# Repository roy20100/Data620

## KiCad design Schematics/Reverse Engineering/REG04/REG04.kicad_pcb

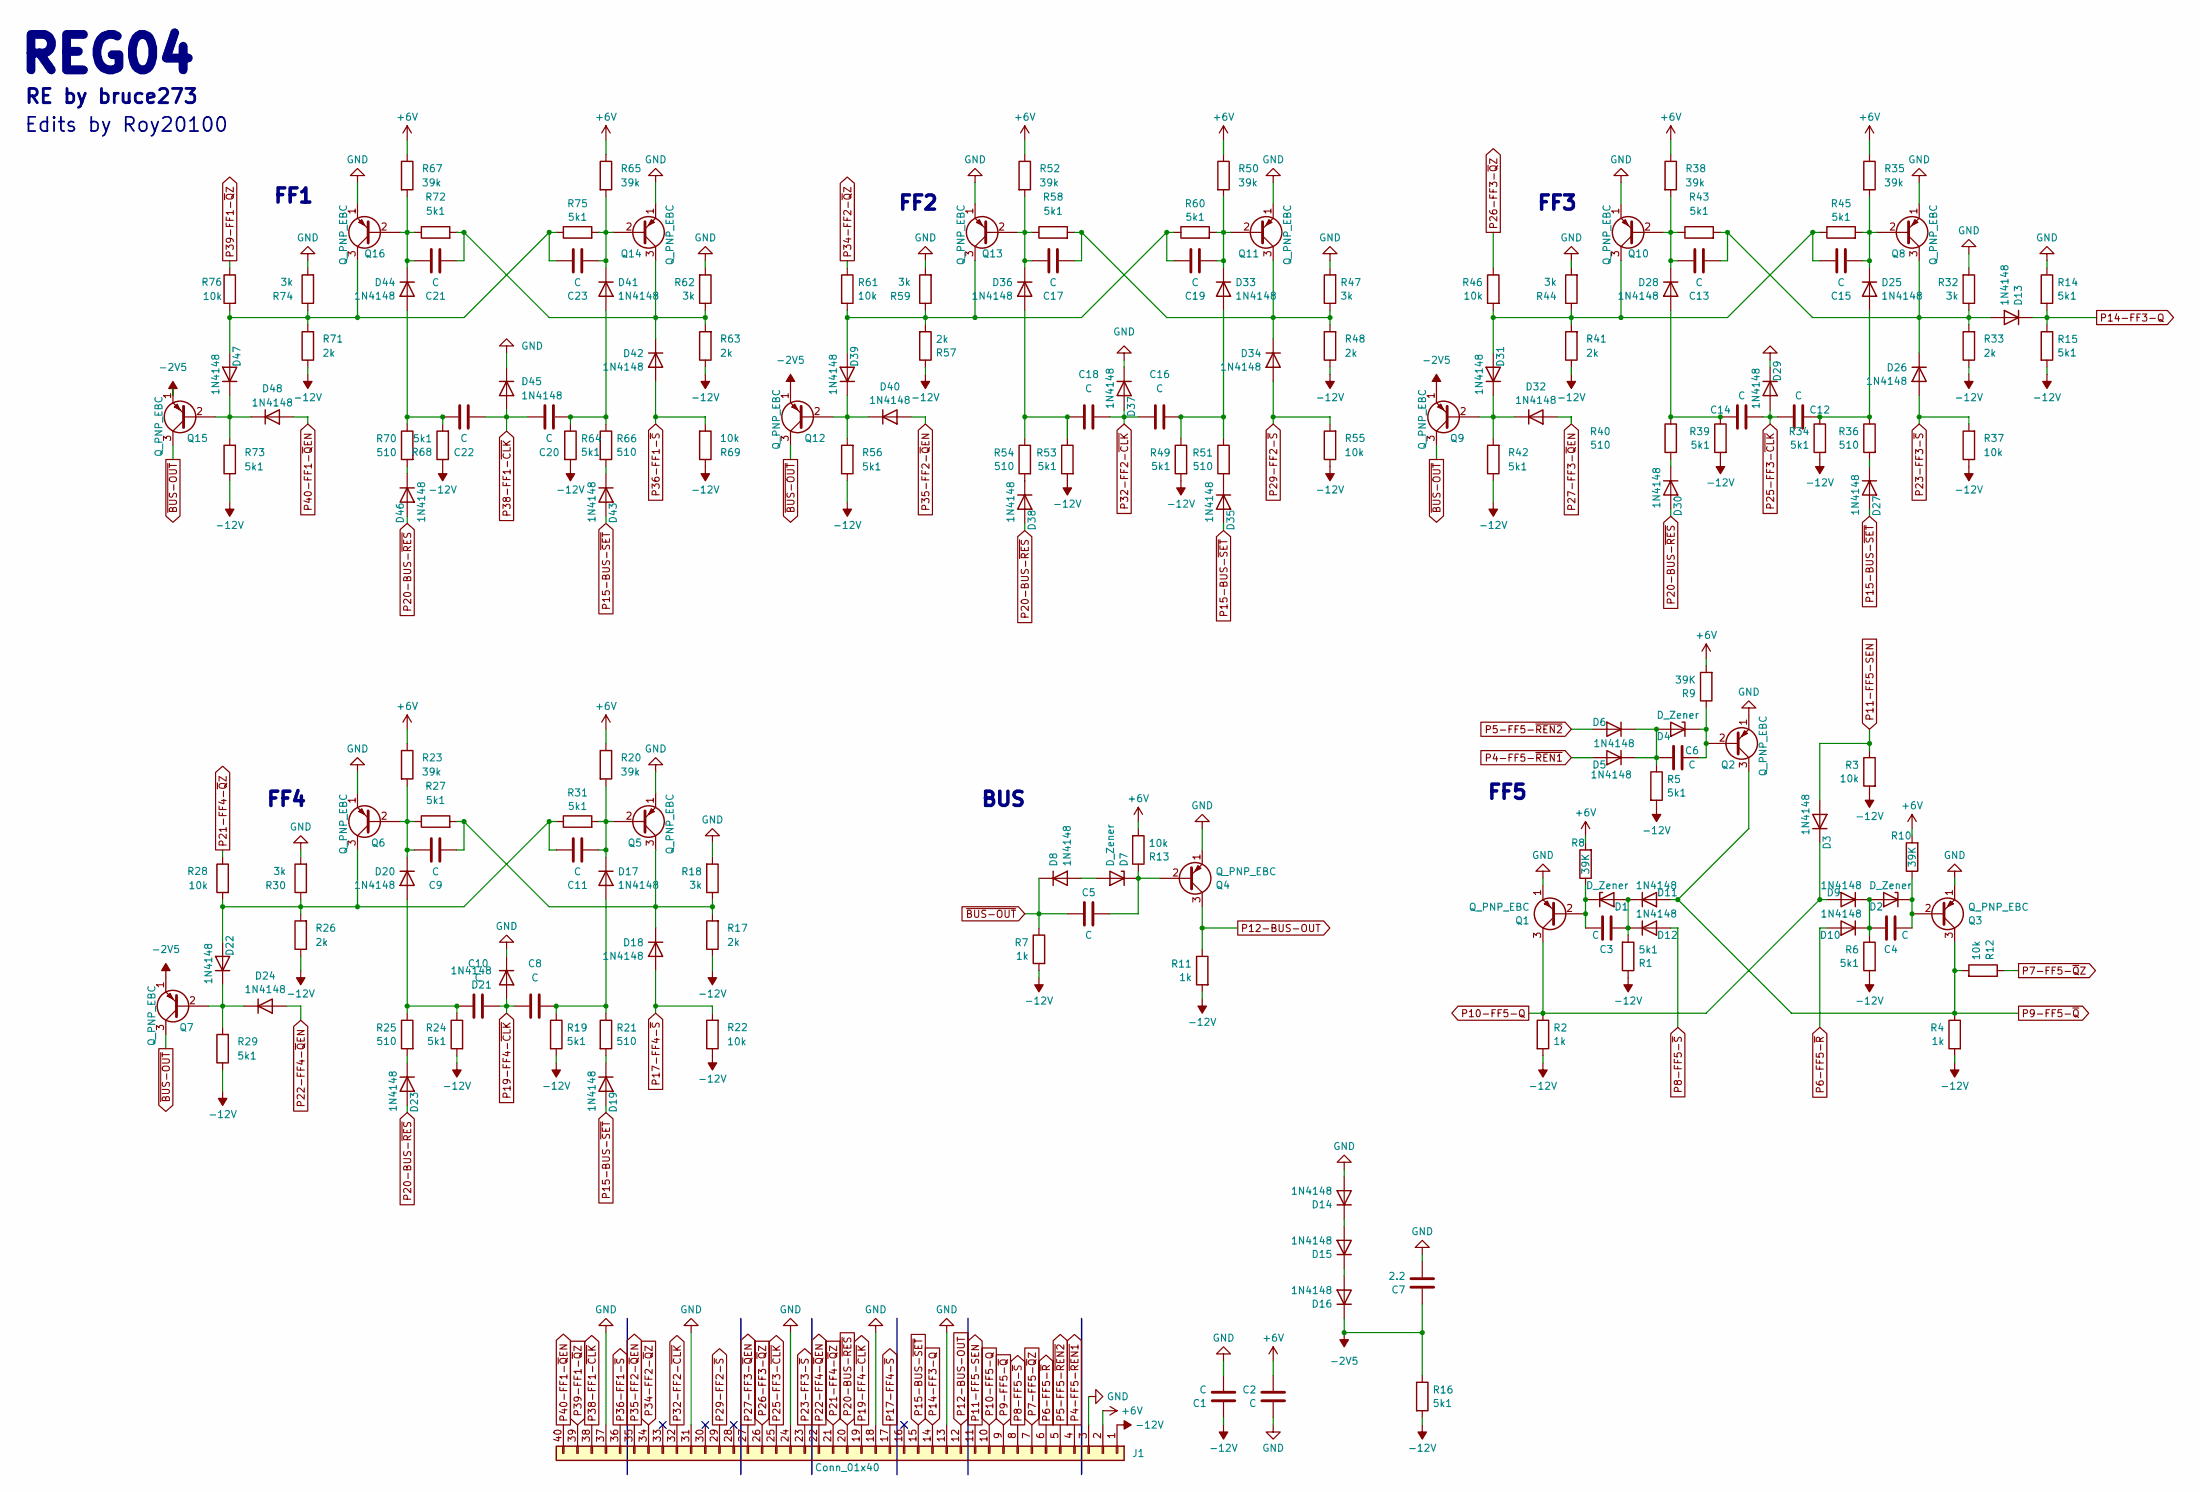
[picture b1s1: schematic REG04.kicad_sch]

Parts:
C1: C; C_Axial_L5.1mm_D3.1mm_P12.50mm_Horizontal
C2: C; C_Axial_L12.0mm_D6.5mm_P15.00mm_Horizontal
C3, C4, C5, C6, C8, C9, C10, C11, C12, C13, C14, C15, C16, C17, C18, C19, C20, C21, C22, C23: C; C_Rect_L7.0mm_W2.0mm_P5.00mm
C7: 2.2; C_Axial_L5.1mm_D3.1mm_P12.50mm_Horizontal
D1, D2, D4, D7: D_Zener; D_A-405_P12.70mm_Horizontal
D3, D5, D6, D8, D9, D10, D11, D12, D13, D14, D15, D16, D17, D18, D19, D20, D21, D22, D23, D24, D25, D26, D27, D28, D29, D30, D31, D32, D33, D34, D35, D36, D37, D38, D39, D40, D41, D42, D43, D44, D45, D46, D47, D48: 1N4148; D_A-405_P12.70mm_Horizontal
J1: Conn_01x40; ELCO 40
Q1, Q2, Q3, Q4, Q5, Q6, Q7, Q8, Q9, Q10, Q11, Q12, Q13, Q14, Q15, Q16: Q_PNP_EBC; TO-5-3
R1: 5k1; R_Axial_DIN0207_L6.3mm_D2.5mm_P10.16mm_Horizontal
R2, R4: 1k; R_Axial_DIN0207_L6.3mm_D2.5mm_P10.16mm_Horizontal
R3: 10k; R_Axial_DIN0207_L6.3mm_D2.5mm_P10.16mm_Horizontal
R5, R6, R14, R15, R16, R19, R24, R27, R29, R31, R34, R39, R42, R43, R45, R49, R53, R56, R58, R60, R64, R68, R72, R73, R75: 5k1; R_Axial_DIN0207_L6.3mm_D2.5mm_P12.7 mm_Horizontal
R7, R11: 1k; R_Axial_DIN0207_L6.3mm_D2.5mm_P12.7 mm_Horizontal
R8, R9: 39K; R_Axial_DIN0207_L6.3mm_D2.5mm_P10.16mm_Horizontal
R10: 39K; R_Axial_DIN0207_L6.3mm_D2.5mm_P12.7 mm_Horizontal
R12, R13, R22, R28, R37, R46, R55, R61, R69, R76: 10k; R_Axial_DIN0207_L6.3mm_D2.5mm_P12.7 mm_Horizontal
R17, R26, R33, R41, R48, R57, R63, R71: 2k; R_Axial_DIN0207_L6.3mm_D2.5mm_P12.7 mm_Horizontal
R18, R30, R32, R44, R47, R59, R62, R74: 3k; R_Axial_DIN0207_L6.3mm_D2.5mm_P12.7 mm_Horizontal
R20, R23, R35, R38, R50, R52, R65, R67: 39k; R_Axial_DIN0207_L6.3mm_D2.5mm_P12.7 mm_Horizontal
R21, R25, R36, R40, R51, R54, R66, R70: 510; R_Axial_DIN0207_L6.3mm_D2.5mm_P12.7 mm_Horizontal

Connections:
+6V: C2.2, J1.2, R8.2, R9.2, R10.2, R13.2, R20.1, R23.1, R35.1, R38.1, R50.1, R52.1, R65.1, R67.1
-2V5: C7.1, D16.1 (K), Q7.1 (E), Q9.1 (E), Q12.1 (E), Q15.1 (E), R16.1
-12V: C1.2, J1.1, R1.1, R2.2, R3.2, R4.2, R5.2, R6.2, R7.2, R11.2, R15.2, R16.2, R17.1, R19.2, R22.1, R24.2, R26.1, R29.1, R33.1, R34.2, R37.1, R39.2, R41.1, R42.1, R48.1, R49.2, R53.2, R55.1, R56.1, R57.1, R63.1, R64.2, R68.1, R69.1, R71.1, R73.1
GND: C1.1, C2.1, C7.2, D14.2 (A), D21.1 (K), D29.1 (K), D37.1 (K), D45.1 (K), J1.3, J1.13, J1.18, J1.24, J1.31, J1.37, Q1.1 (E), Q2.1 (E), Q3.1 (E), Q4.1 (E), Q5.1 (E), Q6.1 (E), Q8.1 (E), Q10.1 (E), Q11.1 (E), Q13.1 (E), Q14.1 (E), Q16.1 (E), R14.1, R18.2, R30.2, R32.2, R44.2, R47.2, R59.2, R62.2, R74.2
unnamed: C3.1, D1.2 (A), D11.1 (K), D12.1 (K), R1.2
unnamed: C3.2, D1.1 (K), Q1.2 (B), R8.1
unnamed: C4.2, D2.1 (K), Q3.2 (B), R10.1
unnamed: C6.2, D4.2 (A), D5.1 (K), D6.1 (K), R5.1
unnamed: C6.1, D4.1 (K), Q2.2 (B), R9.1
unnamed: D7.2 (A), D8.2 (A)
unnamed: C5.2, D7.1 (K), Q4.2 (B), R13.1
unnamed: C4.1, D2.2 (A), D9.1 (K), D10.1 (K), R6.1
unnamed: C13.2, D13.2 (A), D26.1 (K), Q8.3 (C), R32.1, R33.2, R43.2
unnamed: D14.1 (K), D15.2 (A)
unnamed: D15.1 (K), D16.2 (A)
unnamed: C8.2, D17.2 (A), R19.1, R21.1
unnamed: C11.2, D17.1 (K), Q5.2 (B), R20.2, R31.2
unnamed: C9.2, D18.1 (K), Q5.3 (C), R17.2, R18.1, R27.2
unnamed: D19.1 (K), R21.2
unnamed: C10.2, D20.2 (A), R24.1, R25.1
unnamed: C9.1, D20.1 (K), Q6.2 (B), R23.2, R27.1
unnamed: C11.1, D22.2 (A), Q6.3 (C), R26.2, R28.2, R30.1, R31.1
unnamed: D22.1 (K), D24.1 (K), Q7.2 (B), R29.2
unnamed: D23.1 (K), R25.2
unnamed: C12.1, D25.2 (A), R34.1, R36.1
unnamed: C15.2, D25.1 (K), Q8.2 (B), R35.2, R45.2
unnamed: D27.1 (K), R36.2
unnamed: C14.2, D28.2 (A), R39.1, R40.1
unnamed: C13.1, D28.1 (K), Q10.2 (B), R38.2, R43.1
unnamed: D30.1 (K), R40.2
unnamed: C15.1, D31.2 (A), Q10.3 (C), R41.2, R44.1, R45.1, R46.2
unnamed: D31.1 (K), D32.1 (K), Q9.2 (B), R42.2
unnamed: C16.2, D33.2 (A), R49.1, R51.1
unnamed: C19.2, D33.1 (K), Q11.2 (B), R50.2, R60.2
unnamed: C17.2, D34.1 (K), Q11.3 (C), R47.1, R48.2, R58.2
unnamed: D35.1 (K), R51.2
unnamed: C18.2, D36.2 (A), R53.1, R54.1
unnamed: C17.1, D36.1 (K), Q13.2 (B), R52.2, R58.1
unnamed: D38.1 (K), R54.2
unnamed: C19.1, D39.2 (A), Q13.3 (C), R57.2, R59.1, R60.1, R61.2
unnamed: D39.1 (K), D40.1 (K), Q12.2 (B), R56.2
unnamed: C20.2, D41.2 (A), R64.1, R66.1
unnamed: C23.2, D41.1 (K), Q14.2 (B), R65.2, R75.2
unnamed: C21.2, D42.1 (K), Q14.3 (C), R62.1, R63.2, R72.2
unnamed: D43.1 (K), R66.2
unnamed: C22.2, D44.2 (A), R68.2, R70.1
unnamed: C21.1, D44.1 (K), Q16.2 (B), R67.2, R72.1
unnamed: D46.1 (K), R70.2
unnamed: C23.1, D47.2 (A), Q16.3 (C), R71.2, R74.1, R75.1, R76.2
unnamed: D47.1 (K), D48.1 (K), Q15.2 (B), R73.2
P4-FF5-~REN1: D5.2 (A), J1.4
P5-FF5-~REN2: D6.2 (A), J1.5
P6-FF5-~R: D10.2 (A), J1.6
P7-FF5-~QZ: J1.7, R12.1
P8-FF5-~S: D12.2 (A), J1.8
P9-FF5-~Q: D11.2 (A), J1.9, Q2.3 (C), Q3.3 (C), R4.1, R12.2
P10-FF5-Q: D3.1 (K), D9.2 (A), J1.10, Q1.3 (C), R2.1
P11-FF5-SEN: D3.2 (A), J1.11, R3.1
P12-BUS-OUT: J1.12, Q4.3 (C), R11.1
P14-FF3-Q: D13.1 (K), J1.14, R14.2, R15.1
P15-BUS-~SET: D19.2 (A), D27.2 (A), D35.2 (A), D43.2 (A), J1.15
P17-FF4-~S: D18.2 (A), J1.17, R22.2
P19-FF4-~CLK: C8.1, C10.1, D21.2 (A), J1.19
P20-BUS-~RES: D23.2 (A), D30.2 (A), D38.2 (A), D46.2 (A), J1.20
P21-FF4-~QZ: J1.21, R28.1
P22-FF4-~QEN: D24.2 (A), J1.22
P23-FF3-~S: D26.2 (A), J1.23, R37.2
P25-FF3-~CLK: C12.2, C14.1, D29.2 (A), J1.25
P26-FF3-~QZ: J1.26, R46.1
P27-FF3-~QEN: D32.2 (A), J1.27
P29-FF2-~S: D34.2 (A), J1.29, R55.2
P32-FF2-~CLK: C16.1, C18.1, D37.2 (A), J1.32
P34-FF2-~QZ: J1.34, R61.1
P35-FF2-~QEN: D40.2 (A), J1.35
P36-FF1-~S: D42.2 (A), J1.36, R69.2
P38-FF1-~CLK: C20.1, C22.1, D45.2 (A), J1.38
P39-FF1-~QZ: J1.39, R76.1
P40-FF1-~QEN: D48.2 (A), J1.40
~BUS-OUT: C5.1, D8.1 (K), Q7.3 (C), Q9.3 (C), Q12.3 (C), Q15.3 (C), R7.1

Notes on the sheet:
Edits by Roy20100
RE by bruce273
FF2
FF3
BUS
FF1
FF5
FF4
REG04

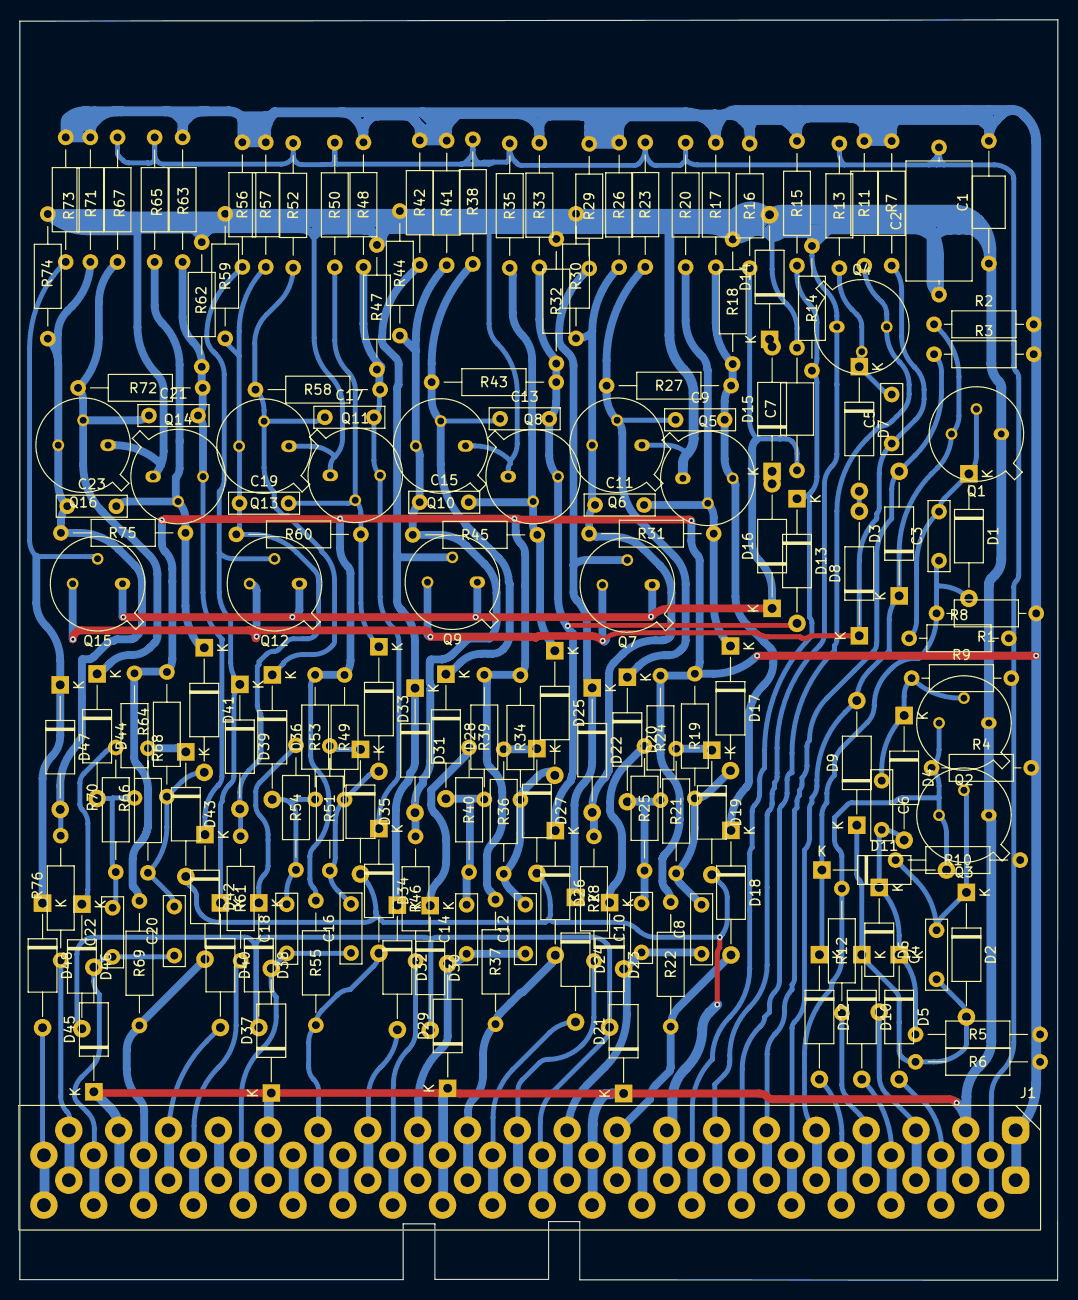
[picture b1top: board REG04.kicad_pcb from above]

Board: 2 copper layers, 105.8 x 128.5 mm, 164 parts (0 on the bottom side), 79 nets.

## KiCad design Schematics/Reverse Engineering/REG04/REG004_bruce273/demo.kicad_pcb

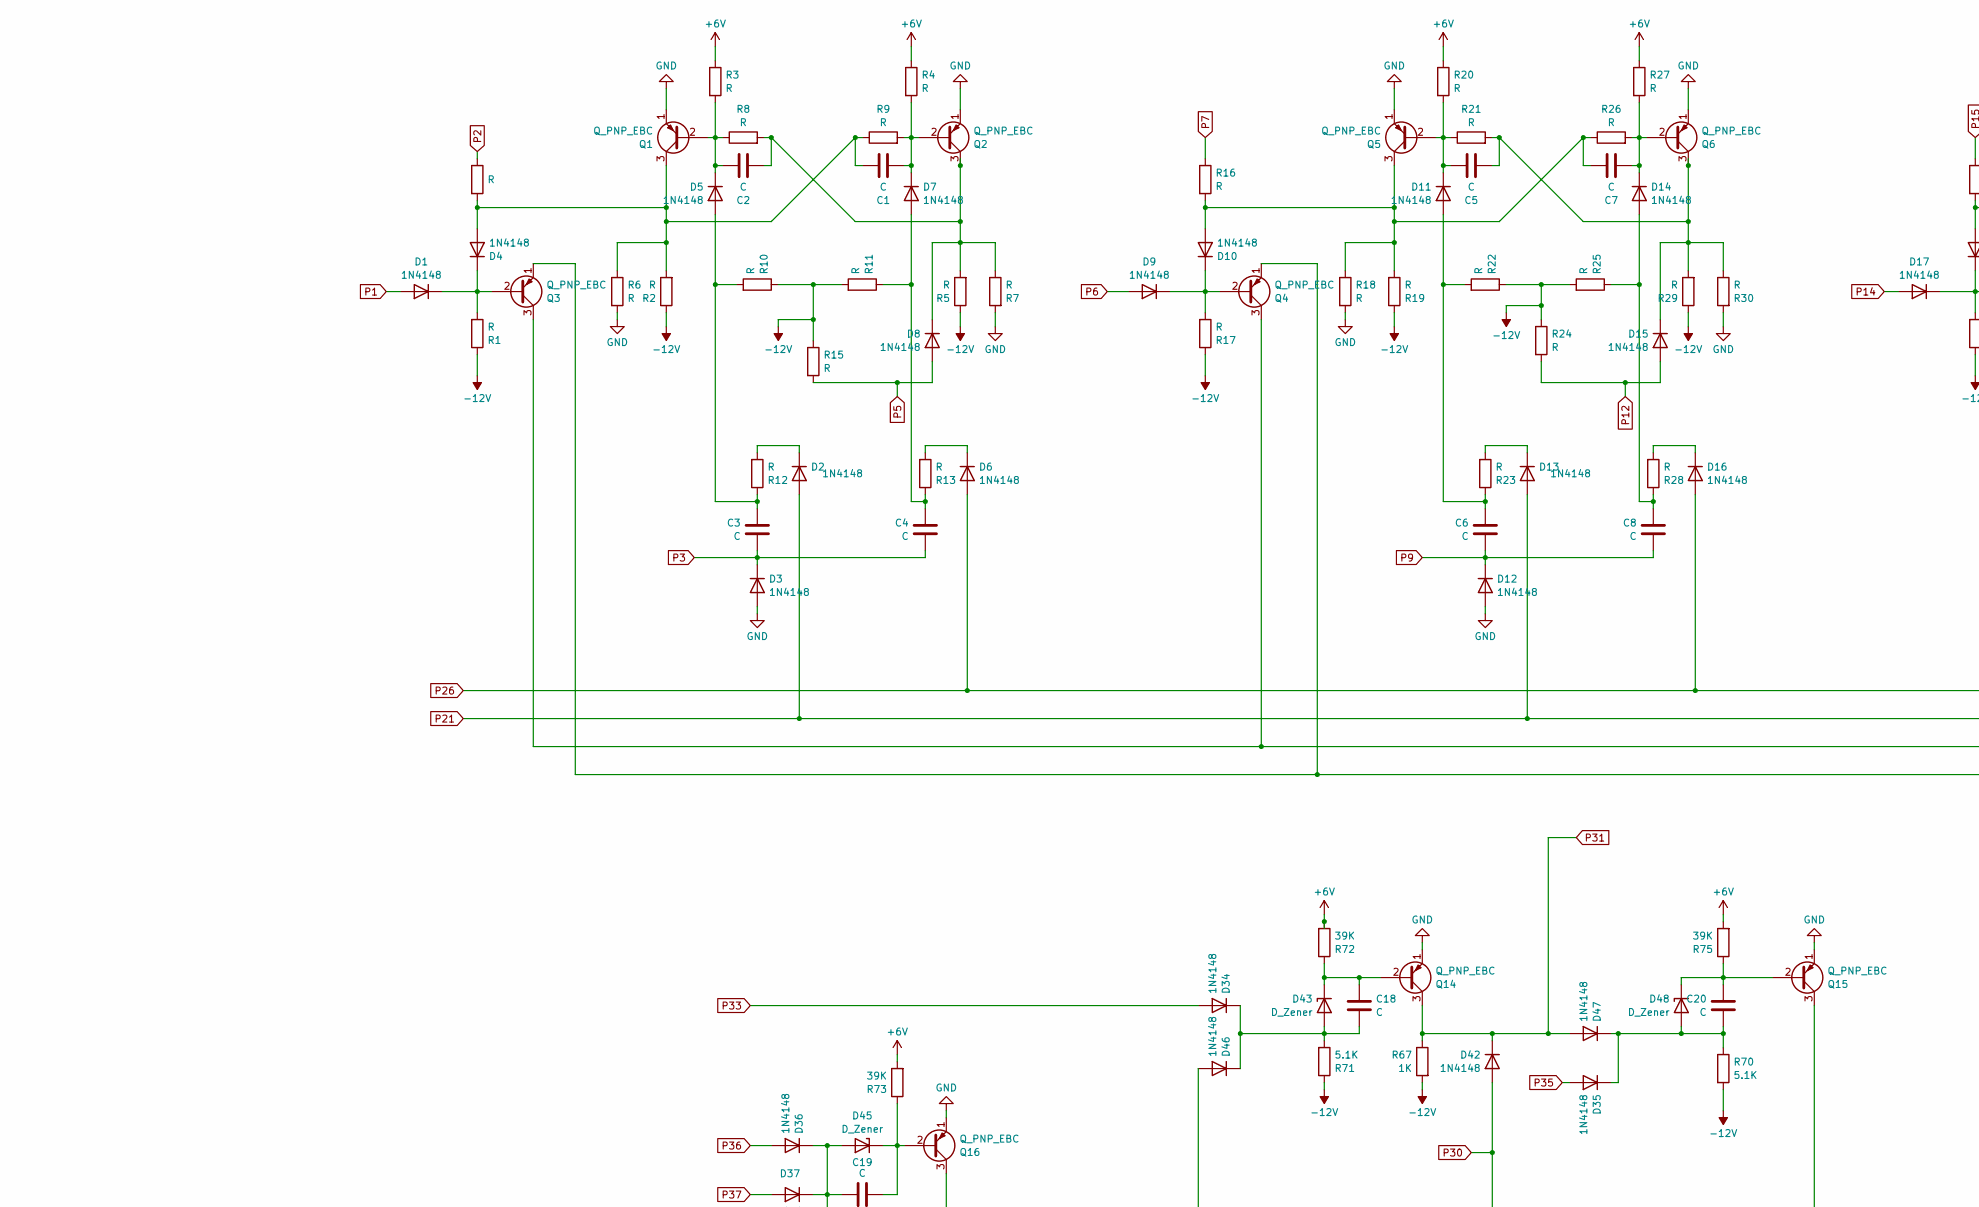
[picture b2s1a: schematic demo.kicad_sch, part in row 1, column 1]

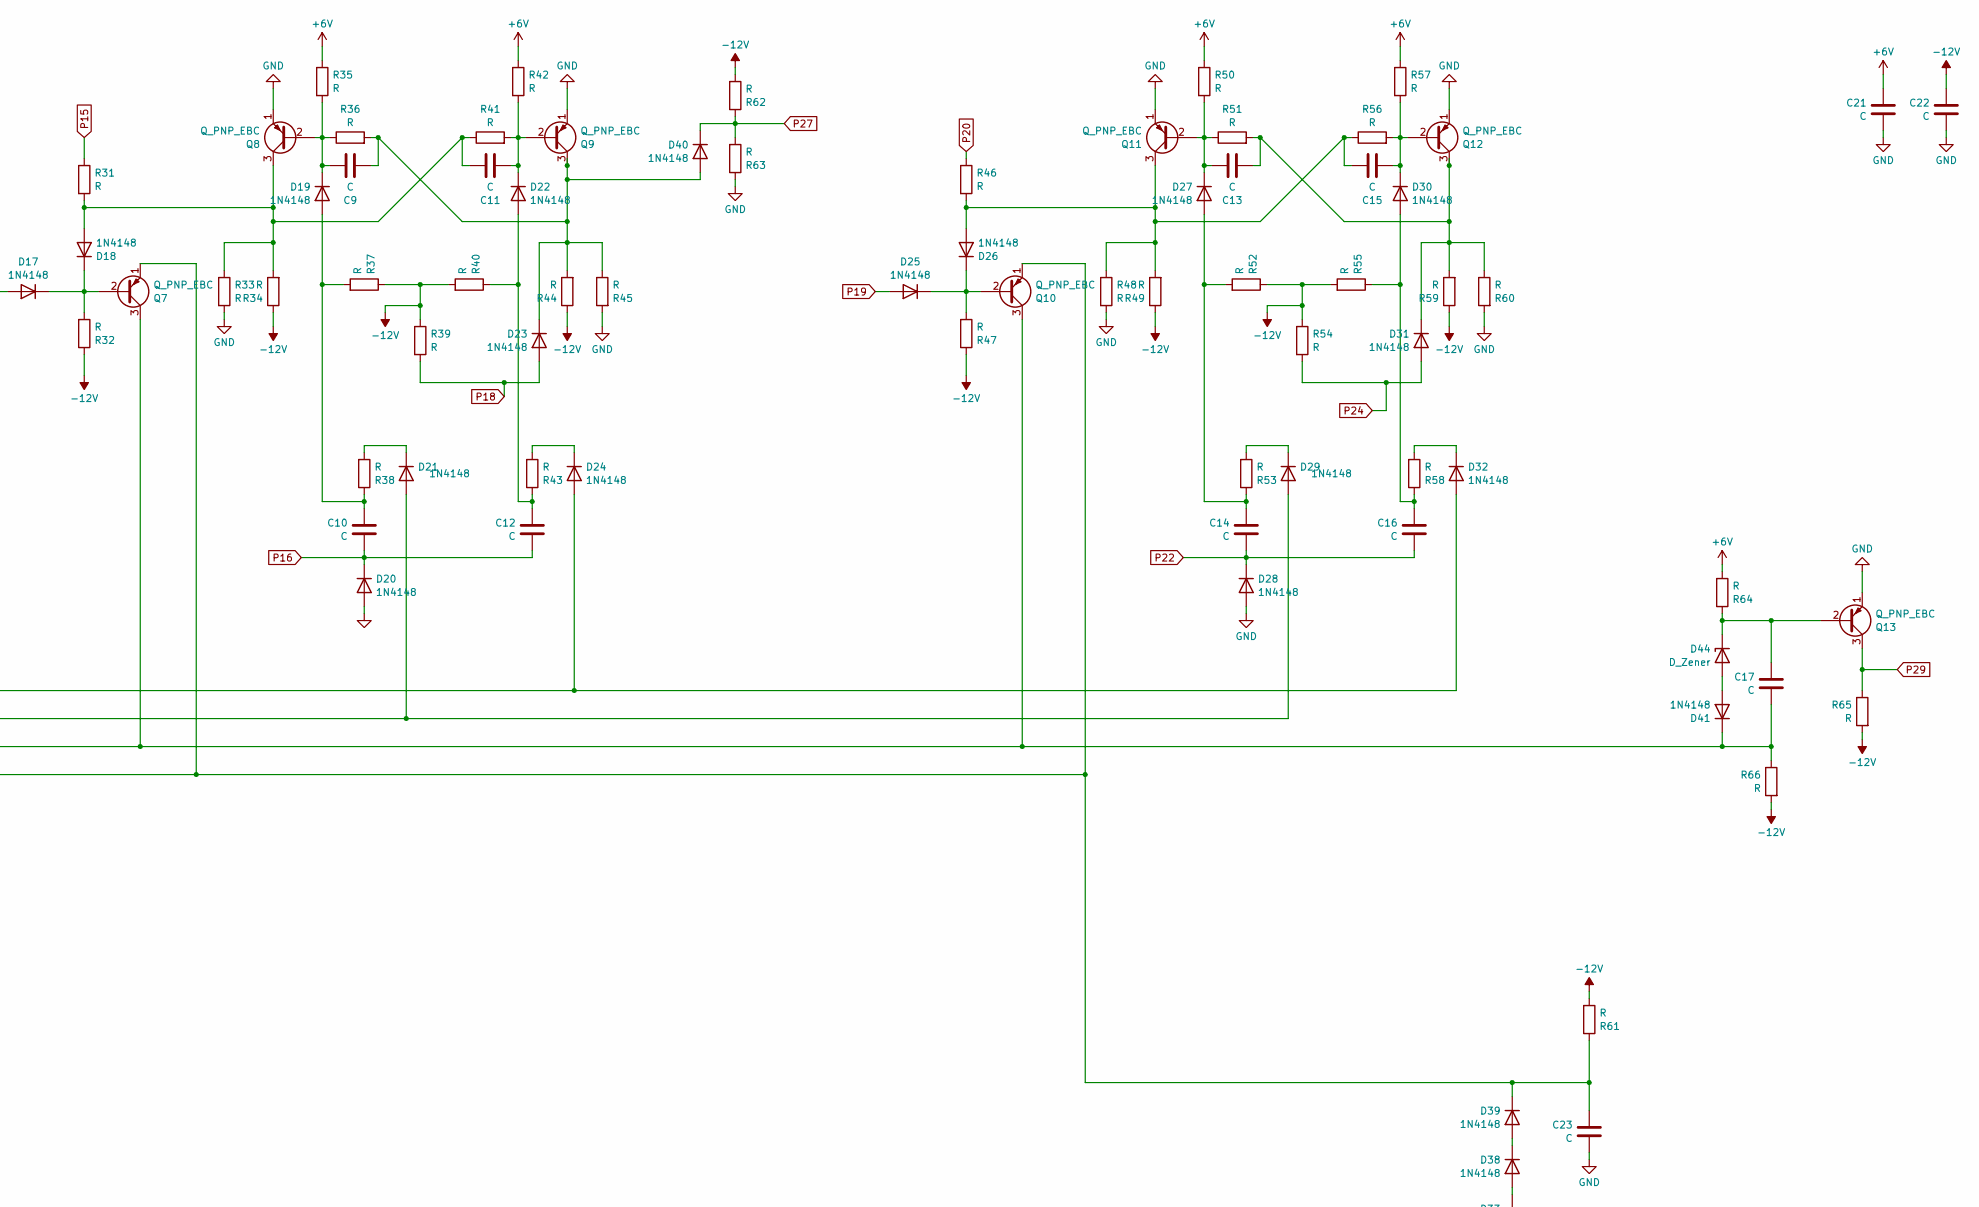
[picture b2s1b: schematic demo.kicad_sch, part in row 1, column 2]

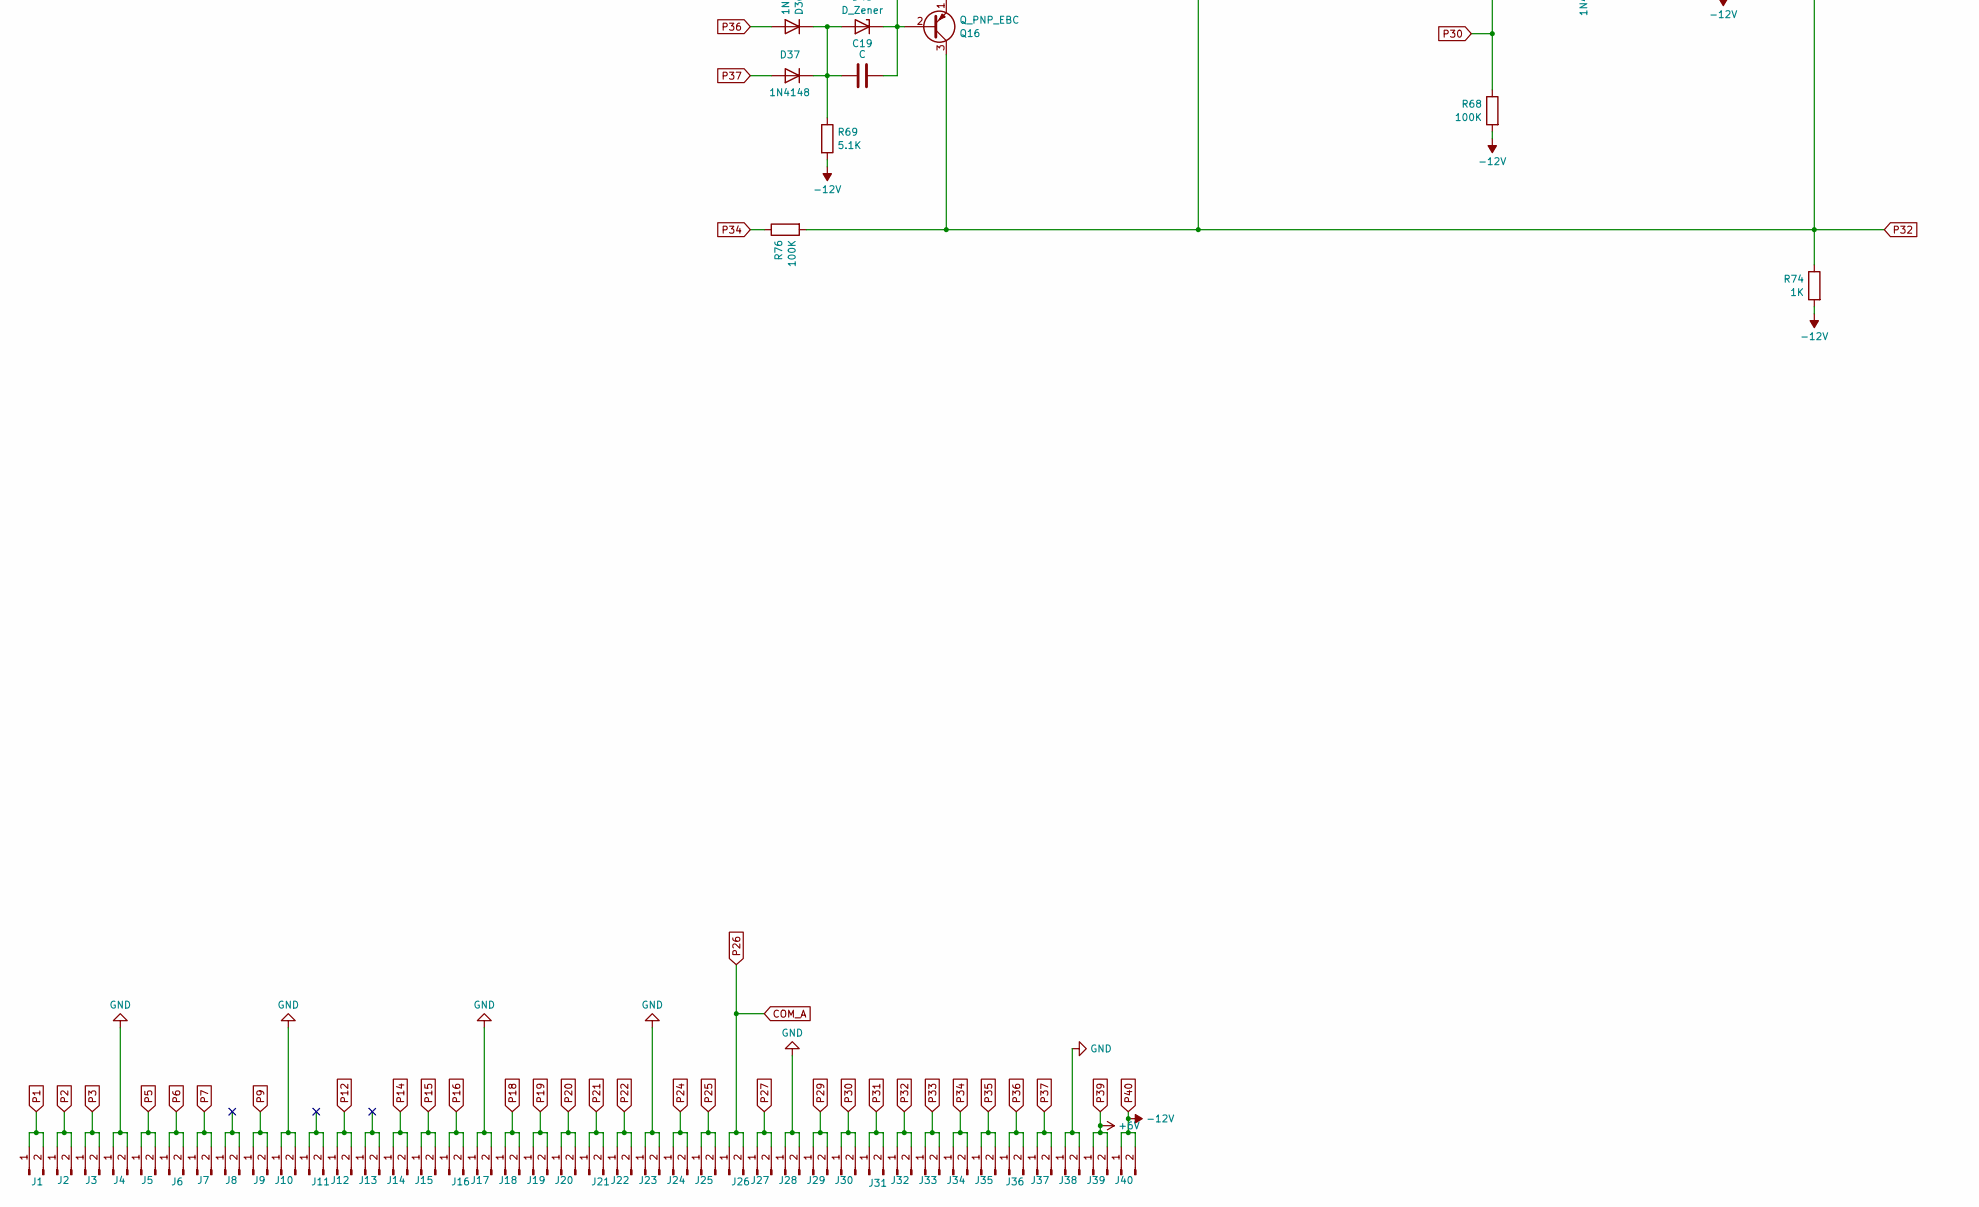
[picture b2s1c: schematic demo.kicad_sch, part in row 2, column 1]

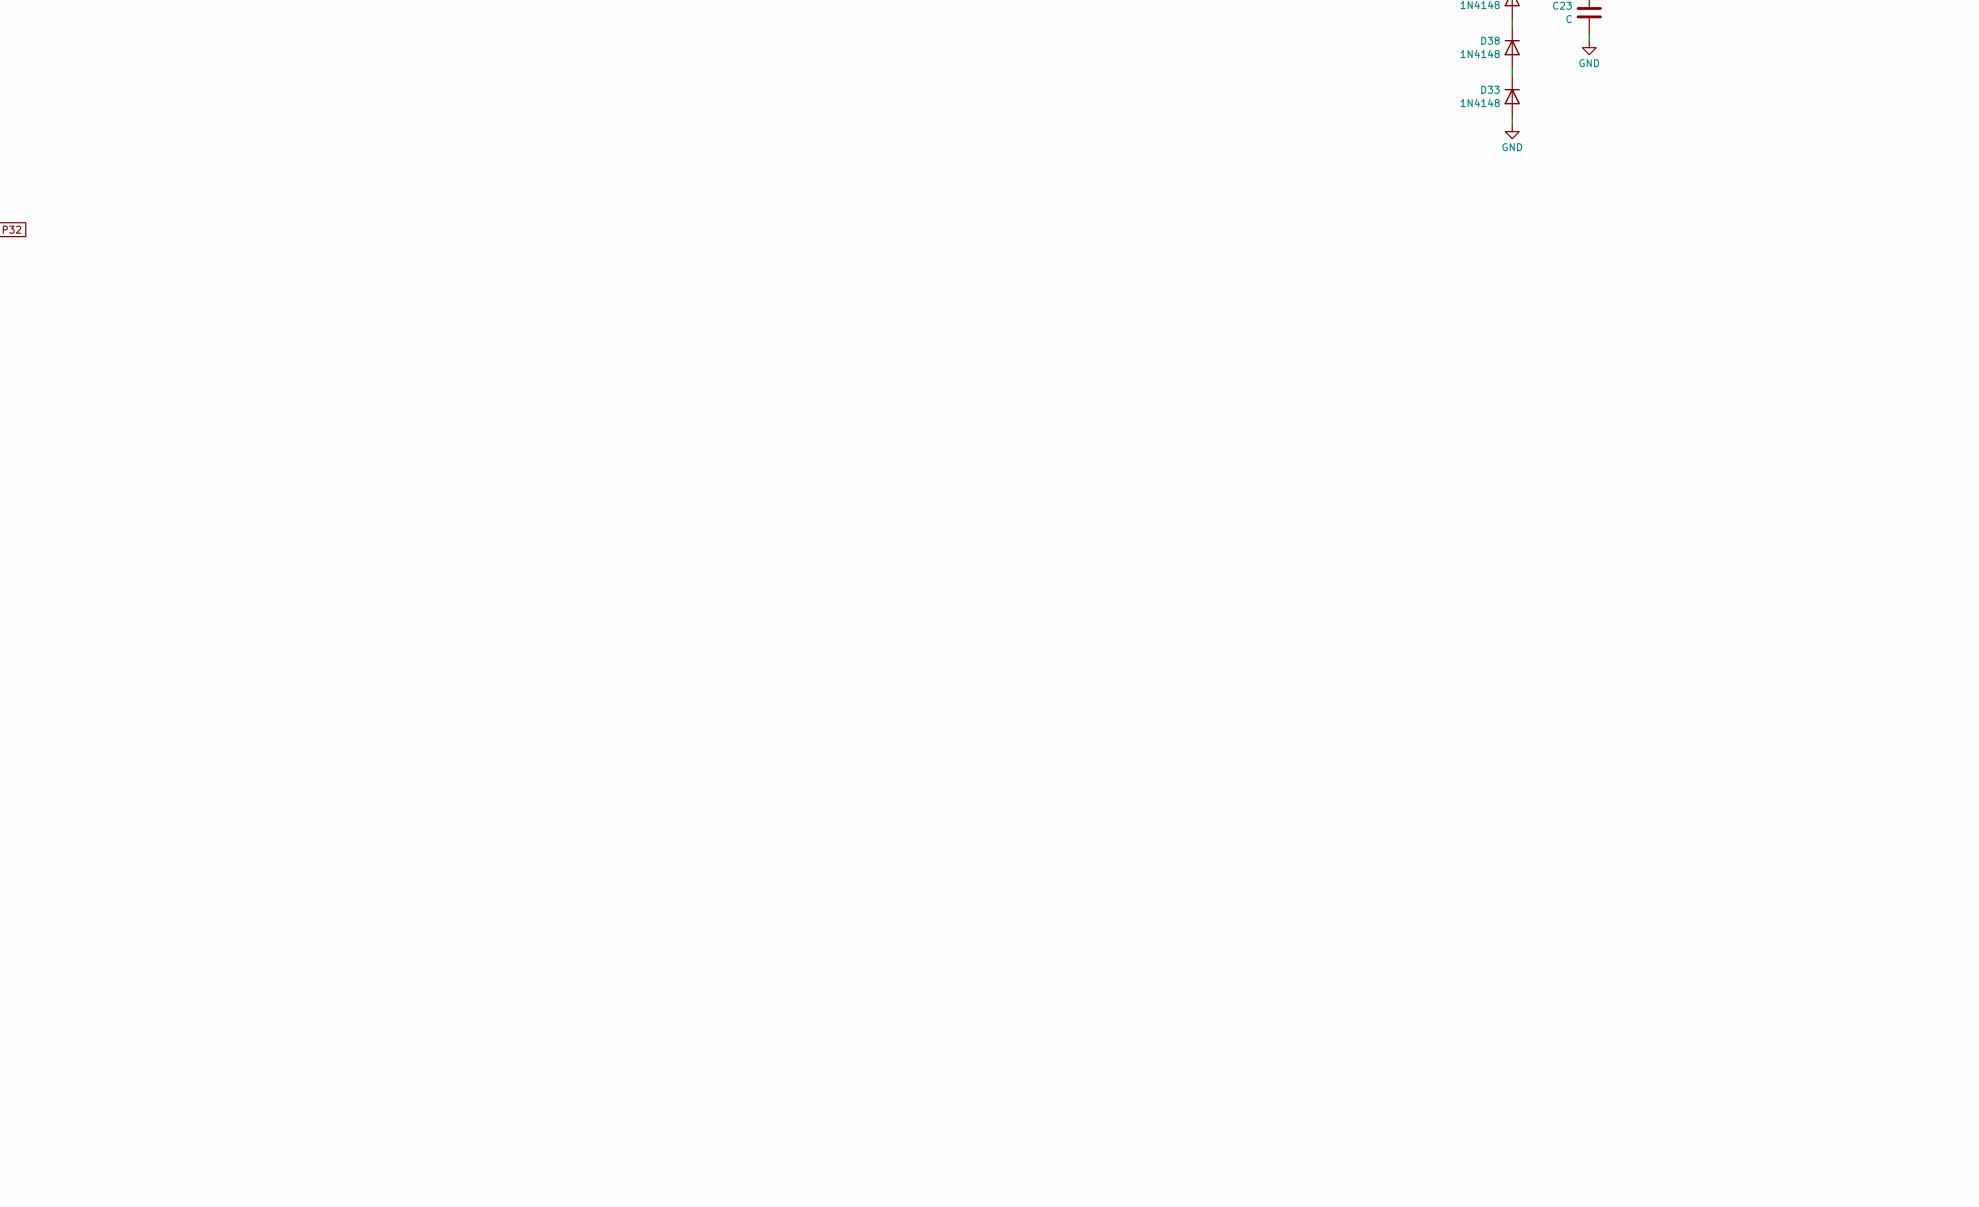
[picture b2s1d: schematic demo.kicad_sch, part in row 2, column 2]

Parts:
C1, C2, C3, C4, C5, C6, C7, C8, C9, C10, C11, C12, C13, C14, C15, C16, C17, C18, C19, C20: C; C_Rect_L7.0mm_W2.0mm_P5.00mm
C21: C; C_Axial_L12.0mm_D6.5mm_P15.00mm_Horizontal
C22, C23: C; C_Axial_L5.1mm_D3.1mm_P12.50mm_Horizontal
D1, D2, D3, D4, D5, D6, D7, D8, D9, D10, D11, D12, D13, D14, D15, D16, D17, D18, D19, D20, D21, D22, D23, D24, D25, D26, D27, D28, D29, D30, D31, D32, D33, D34, D35, D36, D37, D38, D39, D40, D41, D42, D46, D47: 1N4148; D_A-405_P12.70mm_Horizontal
D43, D44, D45, D48: D_Zener; D_A-405_P12.70mm_Horizontal
J1, J2, J3, J4, J5, J6, J7, J8, J9, J10, J11, J12, J13, J14, J15, J16, J17, J18, J19, J20, J21, J22, J23, J24, J25, J26, J27, J28, J29, J30, J31, J32, J33, J34, J35, J36, J37, J38, J39, J40: Conn_01x02_Pin; TestPoint_2Pads_Pitch5.08mm_Drill1.3mm
Q1, Q2, Q3, Q4, Q5, Q6, Q7, Q8, Q9, Q10, Q11, Q12, Q13, Q14, Q15, Q16: Q_PNP_EBC; TO-5-3
R1, R2, R3, R4, R5, R6, R7, R8, R9, R10, R11, R12, R13, R14, R15, R16, R17, R18, R19, R20, R21, R22, R23, R24, R25, R26, R27, R28, R29, R30, R31, R32, R33, R34, R35, R36, R37, R38, R39, R40, R41, R42, R43, R44, R45, R46, R47, R48, R49, R50, R51, R52, R53, R54, R55, R56, R57, R58, R59, R60, R61, R62, R63, R64, R65, R66: R; R_Axial_DIN0207_L6.3mm_D2.5mm_P12.7 mm_Horizontal
R67, R74: 1K; R_Axial_DIN0207_L6.3mm_D2.5mm_P10.16mm_Horizontal
R68: 100K; R_Axial_DIN0207_L6.3mm_D2.5mm_P10.16mm_Horizontal
R69, R70: 5.1K; R_Axial_DIN0207_L6.3mm_D2.5mm_P12.7 mm_Horizontal
R71: 5.1K; R_Axial_DIN0207_L6.3mm_D2.5mm_P10.16mm_Horizontal
R72, R73: 39K; R_Axial_DIN0207_L6.3mm_D2.5mm_P10.16mm_Horizontal
R75: 39K; R_Axial_DIN0207_L6.3mm_D2.5mm_P12.7 mm_Horizontal
R76: 100K; R_Axial_DIN0207_L6.3mm_D2.5mm_P12.7 mm_Horizontal

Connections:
COM_A: D6.2 (A), D16.2 (A), D24.2 (A), D32.2 (A), J26.1, J26.2
GND: C21.1, C22.1, C23.2, D3.2 (A), D12.2 (A), D20.2 (A), D28.2 (A), D33.2 (A), J4.1, J4.2, J10.1, J10.2, J17.1, J17.2, J23.1, J23.2, J28.1, J28.2, J38.1, J38.2, Q1.1 (E), Q2.1 (E), Q5.1 (E), Q6.1 (E), Q8.1 (E), Q9.1 (E), Q11.1 (E), Q12.1 (E), Q13.1 (E), Q14.1 (E), Q15.1 (E), Q16.1 (E), R6.2, R7.2, R18.2, R30.2, R33.2, R45.2, R48.2, R60.2, R63.1
unnamed: D1.1 (K), D4.1 (K), Q3.2 (B), R1.2
unnamed: D2.1 (K), R12.2
unnamed: C1.1, D4.2 (A), Q1.3 (C), R2.2, R6.1, R9.1, R14.2
unnamed: C3.2, D5.2 (A), R10.2, R12.1
unnamed: C2.1, D5.1 (K), Q1.2 (B), R3.2, R8.1
unnamed: D6.1 (K), R13.2
unnamed: C4.2, D7.2 (A), R11.1, R13.1
unnamed: C1.2, D7.1 (K), Q2.2 (B), R4.2, R9.2
unnamed: C2.2, D8.1 (K), Q2.3 (C), R5.2, R7.1, R8.2
unnamed: C7.1, D10.2 (A), Q5.3 (C), R16.2, R18.1, R19.2, R26.1
unnamed: D9.1 (K), D10.1 (K), Q4.2 (B), R17.2
unnamed: C6.2, D11.2 (A), R22.2, R23.1
unnamed: C5.1, D11.1 (K), Q5.2 (B), R20.2, R21.1
unnamed: D13.1 (K), R23.2
unnamed: C8.2, D14.2 (A), R25.1, R28.1
unnamed: C7.2, D14.1 (K), Q6.2 (B), R26.2, R27.2
unnamed: C5.2, D15.1 (K), Q6.3 (C), R21.2, R29.2, R30.1
unnamed: D16.1 (K), R28.2
unnamed: D17.1 (K), D18.1 (K), Q7.2 (B), R32.2
unnamed: C11.1, D18.2 (A), Q8.3 (C), R31.2, R33.1, R34.2, R41.1
unnamed: C10.2, D19.2 (A), R37.2, R38.1
unnamed: C9.1, D19.1 (K), Q8.2 (B), R35.2, R36.1
unnamed: D21.1 (K), R38.2
unnamed: C12.2, D22.2 (A), R40.1, R43.1
unnamed: C11.2, D22.1 (K), Q9.2 (B), R41.2, R42.2
unnamed: C9.2, D23.1 (K), D40.2 (A), Q9.3 (C), R36.2, R44.2, R45.1
unnamed: D24.1 (K), R43.2
unnamed: D25.1 (K), D26.1 (K), Q10.2 (B), R47.2
unnamed: C15.1, D26.2 (A), Q11.3 (C), R46.2, R48.1, R49.2, R56.1
unnamed: C14.2, D27.2 (A), R52.2, R53.1
unnamed: C13.1, D27.1 (K), Q11.2 (B), R50.2, R51.1
unnamed: D29.1 (K), R53.2
unnamed: C16.2, D30.2 (A), R55.1, R58.1
unnamed: C15.2, D30.1 (K), Q12.2 (B), R56.2, R57.2
unnamed: C13.2, D31.1 (K), Q12.3 (C), R51.2, R59.2, R60.1
unnamed: D32.1 (K), R58.2
unnamed: D33.1 (K), D38.2 (A)
unnamed: C18.1, D34.1 (K), D43.2 (A), D46.1 (K), R71.2
unnamed: C20.1, D35.1 (K), D47.1 (K), D48.2 (A), R70.1
unnamed: C19.2, D36.1 (K), D37.1 (K), D45.2 (A), R69.1
unnamed: D38.1 (K), D39.2 (A)
unnamed: C23.1, D39.1 (K), Q3.1 (E), Q4.1 (E), Q7.1 (E), Q10.1 (E), R61.1
unnamed: D41.2 (A), D44.2 (A)
unnamed: C17.1, D41.1 (K), Q3.3 (C), Q4.3 (C), Q7.3 (C), Q10.3 (C), R66.1
unnamed: C18.2, D43.1 (K), Q14.2 (B), R72.1
unnamed: C17.2, D44.1 (K), Q13.2 (B), R64.1
unnamed: C19.1, D45.1 (K), Q16.2 (B), R73.1
unnamed: C20.2, D48.1 (K), Q15.2 (B), R75.1
P1: D1.2 (A), J1.1, J1.2
P2: J2.1, J2.2, R14.1
P3: C3.1, C4.1, D3.1 (K), J3.1, J3.2
P5: D8.2 (A), J5.1, J5.2, R15.2
P6: D9.2 (A), J6.1, J6.2
P7: J7.1, J7.2, R16.1
P9: C6.1, C8.1, D12.1 (K), J9.1, J9.2
P12: D15.2 (A), J12.1, J12.2, R24.2
P14: D17.2 (A), J14.1, J14.2
P15: J15.1, J15.2, R31.1
P16: C10.1, C12.1, D20.1 (K), J16.1, J16.2
P18: D23.2 (A), J18.1, J18.2, R39.2
P19: D25.2 (A), J19.1, J19.2
P20: J20.1, J20.2, R46.1
P21: D2.2 (A), D13.2 (A), D21.2 (A), D29.2 (A), J21.1, J21.2
P22: C14.1, C16.1, D28.1 (K), J22.1, J22.2
P24: D31.2 (A), J24.1, J24.2, R54.2
P25: J25.1, J25.2
P27: D40.1 (K), J27.1, J27.2, R62.1, R63.2
P29: J29.1, J29.2, Q13.3 (C), R65.1
P30: D42.2 (A), J30.1, J30.2, R68.1
P31: D42.1 (K), D47.2 (A), J31.1, J31.2, Q14.3 (C), R67.1
P32: D46.2 (A), J32.1, J32.2, Q15.3 (C), Q16.3 (C), R74.1, R76.2
P33: D34.2 (A), J33.1, J33.2
P34: J34.1, J34.2, R76.1
P35: D35.2 (A), J35.1, J35.2
P36: D36.2 (A), J36.1, J36.2
P37: D37.2 (A), J37.1, J37.2
P39: C21.2, J39.1, J39.2, R3.1, R4.1, R20.1, R27.1, R35.1, R42.1, R50.1, R57.1, R64.2, R72.2, R73.2, R75.2
P40: C22.2, J40.1, J40.2, R1.1, R2.1, R5.1, R10.1, R11.2, R15.1, R17.1, R19.1, R22.1, R24.1, R25.2, R29.1, R32.1, R34.1, R37.1, R39.1, R40.2, R44.1, R47.1, R49.1, R52.1, R54.1, R55.2, R59.1, R61.2, R62.2, R65.2, R66.2, R67.2, R68.2, R69.2, R70.2, R71.1, R74.2

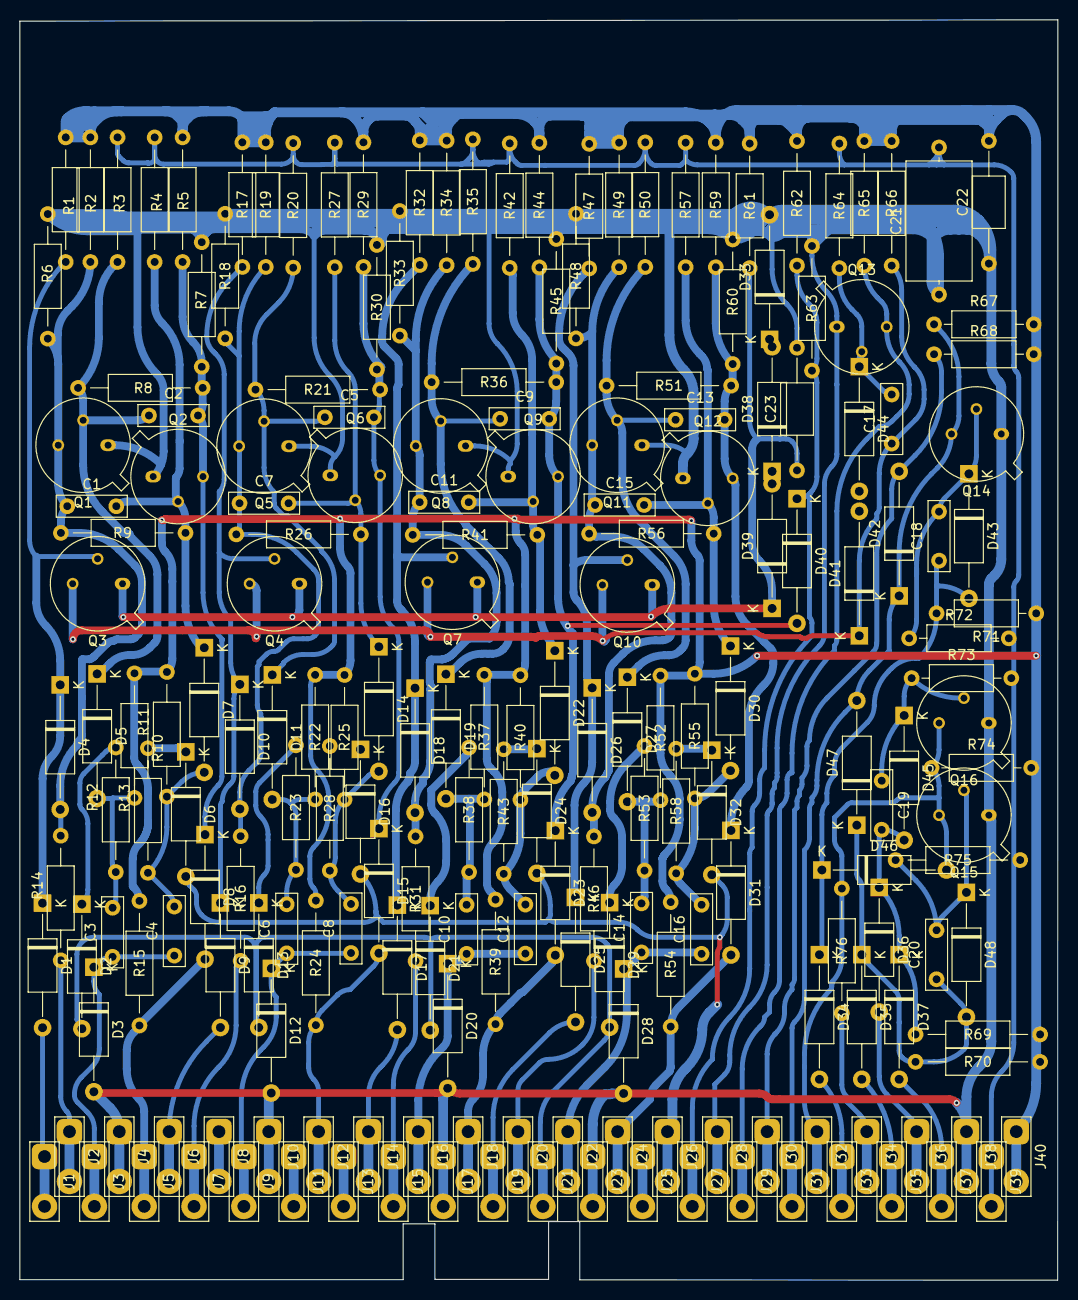
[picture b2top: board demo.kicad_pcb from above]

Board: 2 copper layers, 105.8 x 128.5 mm, 203 parts (0 on the bottom side), 80 nets.
